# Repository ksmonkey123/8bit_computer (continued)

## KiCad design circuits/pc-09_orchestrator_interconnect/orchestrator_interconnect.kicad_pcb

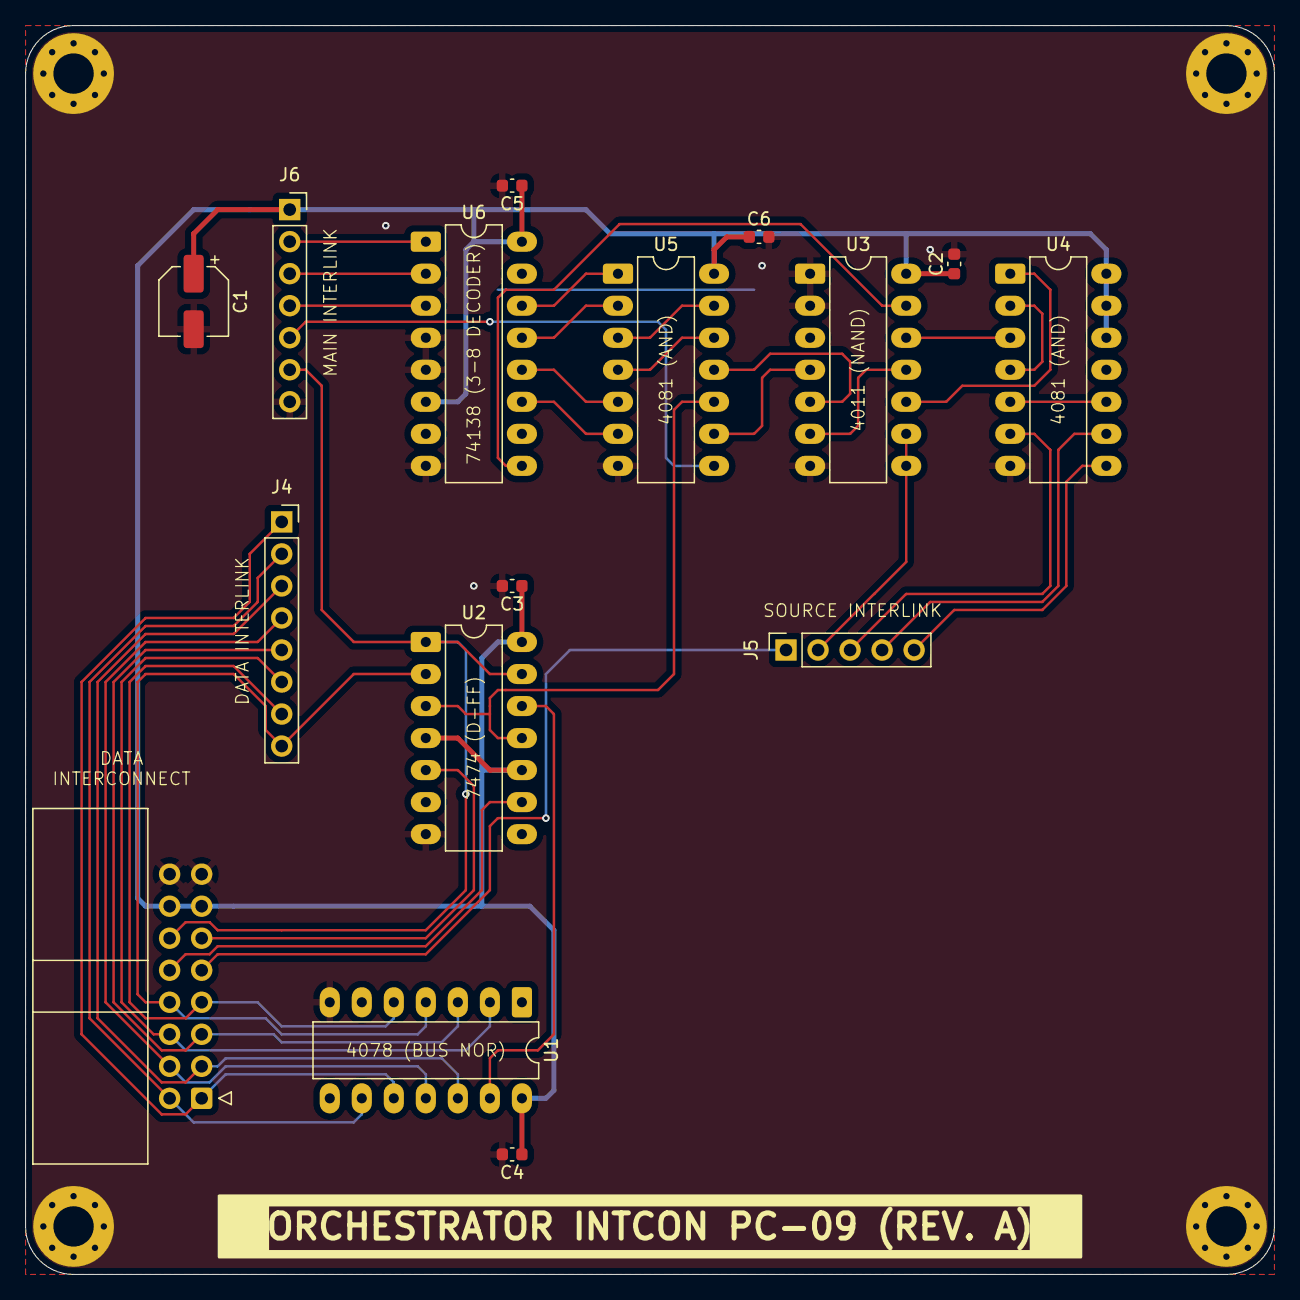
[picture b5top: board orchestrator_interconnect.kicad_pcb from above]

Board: 2 copper layers, 99.1 x 99.1 mm, 20 parts (0 on the bottom side), 38 nets.

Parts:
C1: C_Polarized; CP_Elec_5x5.3
C2, C3, C4, C5, C6: C; C_0603_1608Metric
DATA_BUS1: Conn_01x16; IDC-Header_2x08_P2.54mm_Horizontal
H1, H2, H3, H4: MountingHole_Pad; MountingHole_3.2mm_M3_Pad_Via
J4: Conn_01x08; PinSocket_1x08_P2.54mm_Vertical
J5: Conn_01x05; PinSocket_1x05_P2.54mm_Vertical
J6: Conn_01x07; PinSocket_1x07_P2.54mm_Vertical
U1: 4078; DIP-14_W7.62mm_LongPads
U2: 74HC74; DIP-14_W7.62mm_LongPads
U3: 4011; DIP-14_W7.62mm_LongPads
U4, U5: 4081; DIP-14_W7.62mm_LongPads
U6: 74HC138; DIP-16_W7.62mm_LongPads

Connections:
/carryFlag: DATA_BUS1.9, J5.1
/clock: J6.5, U5.8
/data0: DATA_BUS1.1, J4.1, U1.10
/data1: DATA_BUS1.2, J4.2, U1.9
/data2: DATA_BUS1.3, J4.3, U1.12
/data3: DATA_BUS1.4, J4.4, U1.11
/data4: DATA_BUS1.5, J4.5, U1.3
/data5: DATA_BUS1.6, J4.6, U1.2
/data6: DATA_BUS1.7, J4.7, U1.5
/data7: DATA_BUS1.8, J4.8, U1.4, U2.2 (D)
/dsrc0: J5.2, U3.8, U3.9
/dsrc1: J5.3, U4.6
/dsrc2: J5.4, U4.9
/dsrc3: J5.5, U4.8
/dtgt0: J6.2, U6.1 (A0)
/dtgt1: J6.3, U6.2 (A1)
/dtgt2: J6.4, U6.3 (A2)
/minusFlag: DATA_BUS1.11, U2.5 (Q)
/updateFlags: U2.3 (C), U2.11 (C), U5.10
/zeroFlag: DATA_BUS1.10, U2.9 (Q)
/zeroOnBus: U1.13, U2.12 (D)
/~reset: DATA_BUS1.12, J6.6, U2.1 (~R), U2.13 (~R)
GND: C1.2, C2.2, C3.2, C4.2, C5.2, C6.2, DATA_BUS1.15, DATA_BUS1.16, H1.1, H2.1, H3.1, H4.1, J6.7, U1.7 (Vss), U2.7 (GND), U3.1, U3.2, U3.7 (VSS), U4.7 (VSS), U5.7 (VSS), U6.4 (~E0), U6.5 (~E1), U6.8 (GND)
unnamed: U3.4, U5.9
unnamed: U3.5, U5.11
unnamed: U3.10, U4.1
unnamed: U3.6, U3.11
unnamed: U3.12, U4.3
unnamed: U4.2, U4.4
unnamed: U4.5, U4.10
unnamed: U5.4, U5.12
unnamed: U5.3, U5.13
unnamed: U5.1, U6.14 (~Y1)
unnamed: U5.2, U6.13 (~Y2)
unnamed: U5.5, U6.12 (~Y3)
unnamed: U5.6, U6.11 (~Y4)
unnamed: U3.13, U6.9 (~Y6)
VCC: C1.1, C2.1, C3.1, C4.1, C5.1, C6.1, DATA_BUS1.13, DATA_BUS1.14, J6.1, U1.14 (Vdd), U2.4 (~S), U2.10 (~S), U2.14 (VCC), U3.14 (VDD), U4.12, U4.13, U4.14 (VDD), U5.14 (VDD), U6.6 (E2), U6.16 (VCC)

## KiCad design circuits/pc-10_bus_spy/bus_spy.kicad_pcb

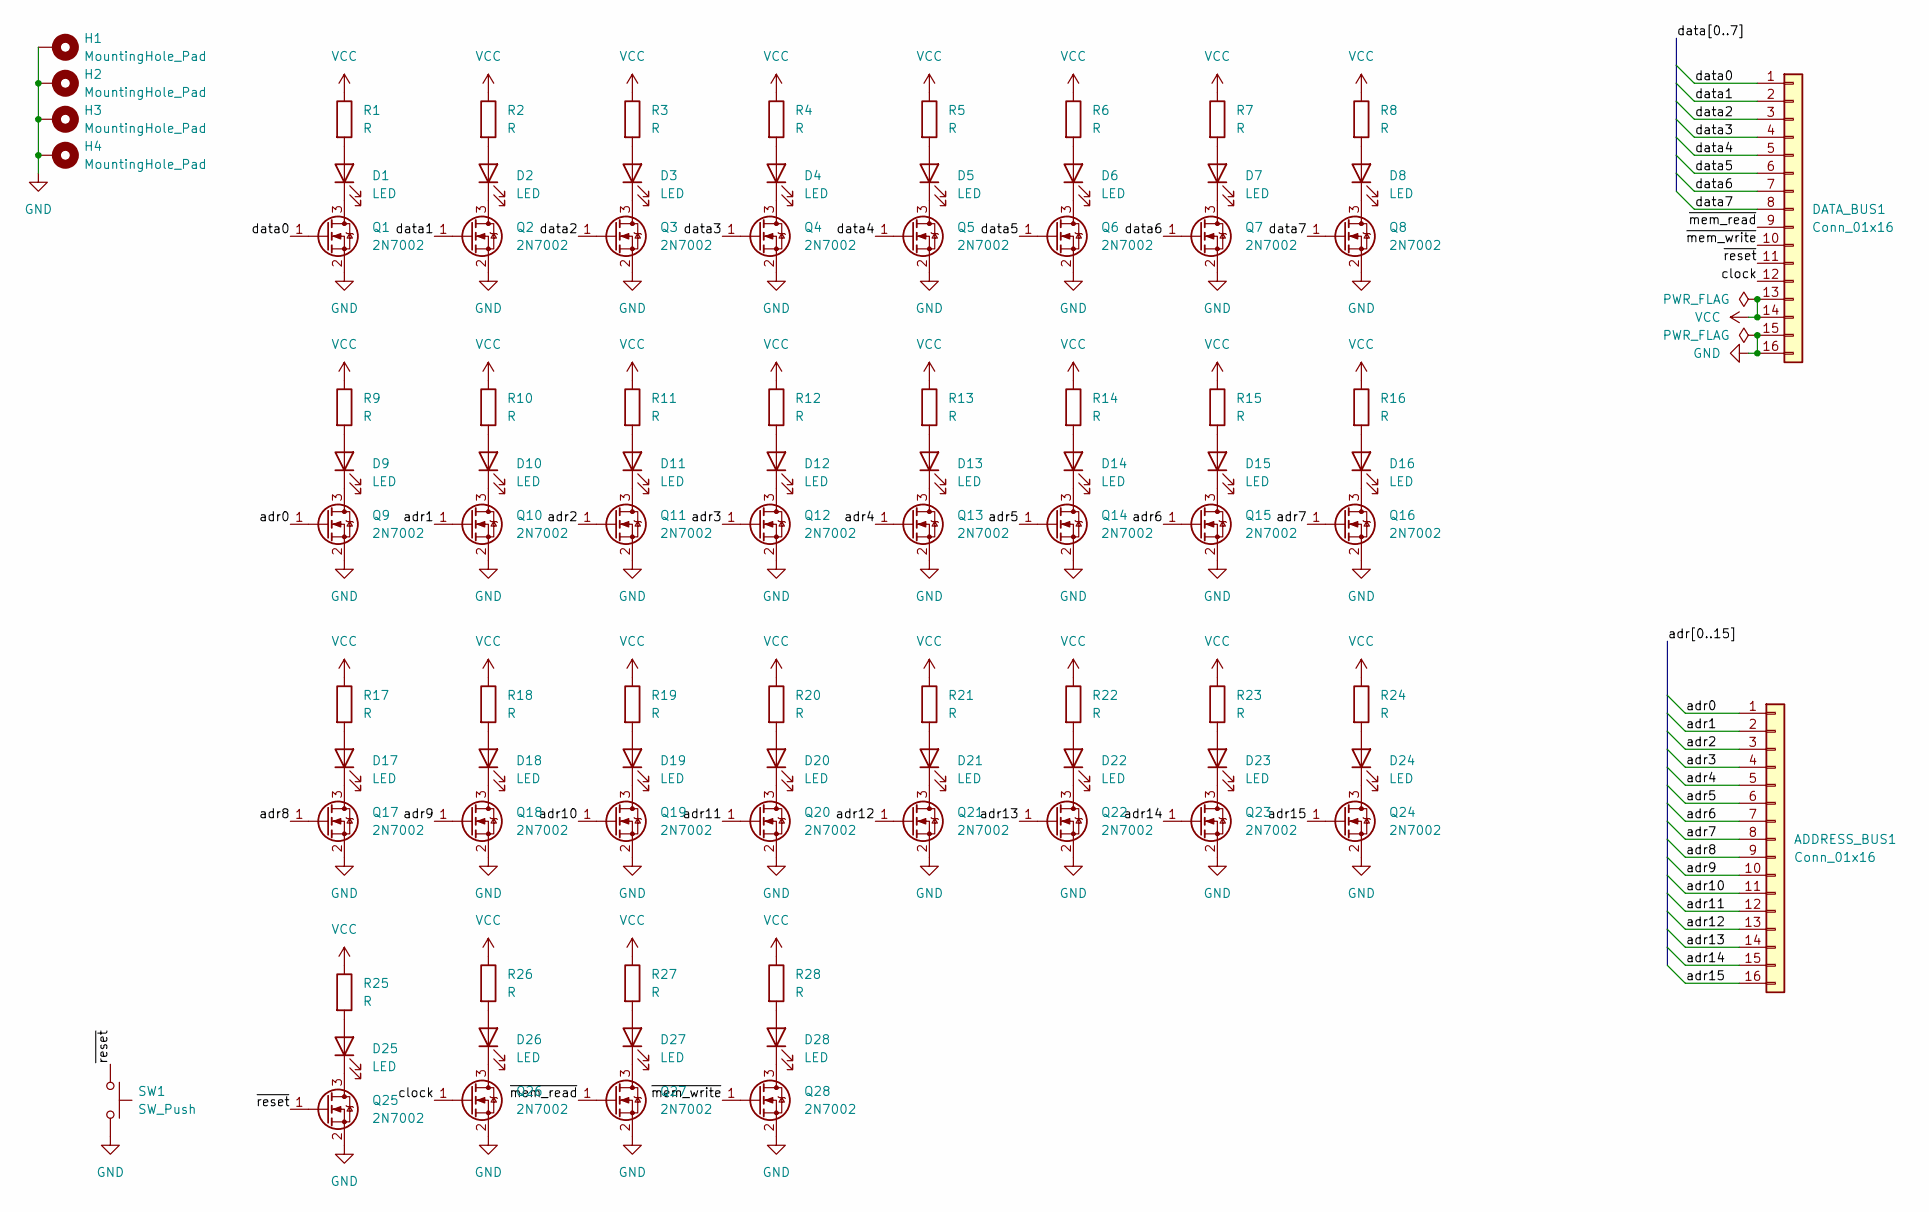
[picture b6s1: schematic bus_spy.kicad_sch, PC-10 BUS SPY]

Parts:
ADDRESS_BUS1: Conn_01x16; IDC-Header_2x08_P2.54mm_Horizontal
D1, D2, D3, D4, D5, D6, D7, D8, D9, D10, D11, D12, D13, D14, D15, D16, D17, D18, D19, D20, D21, D22, D23, D24, D25, D26, D27, D28: LED; LED_0603_1608Metric
DATA_BUS1: Conn_01x16; IDC-Header_2x08_P2.54mm_Horizontal
H1, H2, H3, H4: MountingHole_Pad; MountingHole_3.2mm_M3_Pad_Via
Q1, Q2, Q3, Q4, Q5, Q6, Q7, Q8, Q9, Q10, Q11, Q12, Q13, Q14, Q15, Q16, Q17, Q18, Q19, Q20, Q21, Q22, Q23, Q24, Q25, Q26, Q27, Q28: 2N7002; SOT-23
R1, R2, R3, R4, R5, R6, R7, R8, R9, R10, R11, R12, R13, R14, R15, R16, R17, R18, R19, R20, R21, R22, R23, R24, R25, R26, R27, R28: R; R_0603_1608Metric
SW1: SW_Push; SW_PUSH_6mm

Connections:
/adr0: ADDRESS_BUS1.1, Q9.1 (G)
/adr1: ADDRESS_BUS1.2, Q10.1 (G)
/adr2: ADDRESS_BUS1.3, Q11.1 (G)
/adr3: ADDRESS_BUS1.4, Q12.1 (G)
/adr4: ADDRESS_BUS1.5, Q13.1 (G)
/adr5: ADDRESS_BUS1.6, Q14.1 (G)
/adr6: ADDRESS_BUS1.7, Q15.1 (G)
/adr7: ADDRESS_BUS1.8, Q16.1 (G)
/adr8: ADDRESS_BUS1.9, Q17.1 (G)
/adr9: ADDRESS_BUS1.10, Q18.1 (G)
/adr10: ADDRESS_BUS1.11, Q19.1 (G)
/adr11: ADDRESS_BUS1.12, Q20.1 (G)
/adr12: ADDRESS_BUS1.13, Q21.1 (G)
/adr13: ADDRESS_BUS1.14, Q22.1 (G)
/adr14: ADDRESS_BUS1.15, Q23.1 (G)
/adr15: ADDRESS_BUS1.16, Q24.1 (G)
/clock: DATA_BUS1.12, Q26.1 (G)
/data0: DATA_BUS1.1, Q1.1 (G)
/data1: DATA_BUS1.2, Q2.1 (G)
/data2: DATA_BUS1.3, Q3.1 (G)
/data3: DATA_BUS1.4, Q4.1 (G)
/data4: DATA_BUS1.5, Q5.1 (G)
/data5: DATA_BUS1.6, Q6.1 (G)
/data6: DATA_BUS1.7, Q7.1 (G)
/data7: DATA_BUS1.8, Q8.1 (G)
/~mem_read: DATA_BUS1.9, Q27.1 (G)
/~mem_write: DATA_BUS1.10, Q28.1 (G)
/~reset: DATA_BUS1.11, Q25.1 (G), SW1.1
GND: DATA_BUS1.15, DATA_BUS1.16, H1.1, H2.1, H3.1, H4.1, Q1.2 (S), Q2.2 (S), Q3.2 (S), Q4.2 (S), Q5.2 (S), Q6.2 (S), Q7.2 (S), Q8.2 (S), Q9.2 (S), Q10.2 (S), Q11.2 (S), Q12.2 (S), Q13.2 (S), Q14.2 (S), Q15.2 (S), Q16.2 (S), Q17.2 (S), Q18.2 (S), Q19.2 (S), Q20.2 (S), Q21.2 (S), Q22.2 (S), Q23.2 (S), Q24.2 (S), Q25.2 (S), Q26.2 (S), Q27.2 (S), Q28.2 (S), SW1.2; also elsewhere on the board
unnamed: D1.2 (A), R1.2
unnamed: D1.1 (K), Q1.3 (D)
unnamed: D2.2 (A), R2.2
unnamed: D2.1 (K), Q2.3 (D)
unnamed: D3.2 (A), R3.2
unnamed: D3.1 (K), Q3.3 (D)
unnamed: D4.2 (A), R4.2
unnamed: D4.1 (K), Q4.3 (D)
unnamed: D5.2 (A), R5.2
unnamed: D5.1 (K), Q5.3 (D)
unnamed: D6.2 (A), R6.2
unnamed: D6.1 (K), Q6.3 (D)
unnamed: D7.2 (A), R7.2
unnamed: D7.1 (K), Q7.3 (D)
unnamed: D8.2 (A), R8.2
unnamed: D8.1 (K), Q8.3 (D)
unnamed: D9.2 (A), R9.2
unnamed: D9.1 (K), Q9.3 (D)
unnamed: D10.2 (A), R10.2
unnamed: D10.1 (K), Q10.3 (D)
unnamed: D11.2 (A), R11.2
unnamed: D11.1 (K), Q11.3 (D)
unnamed: D12.2 (A), R12.2
unnamed: D12.1 (K), Q12.3 (D)
unnamed: D13.2 (A), R13.2
unnamed: D13.1 (K), Q13.3 (D)
unnamed: D14.2 (A), R14.2
unnamed: D14.1 (K), Q14.3 (D)
unnamed: D15.2 (A), R15.2
unnamed: D15.1 (K), Q15.3 (D)
unnamed: D16.2 (A), R16.2
unnamed: D16.1 (K), Q16.3 (D)
unnamed: D17.2 (A), R17.2
unnamed: D17.1 (K), Q17.3 (D)
unnamed: D18.2 (A), R18.2
unnamed: D18.1 (K), Q18.3 (D)
unnamed: D19.2 (A), R19.2
unnamed: D19.1 (K), Q19.3 (D)
unnamed: D20.2 (A), R20.2
unnamed: D20.1 (K), Q20.3 (D)
unnamed: D21.2 (A), R21.2
unnamed: D21.1 (K), Q21.3 (D)
unnamed: D22.2 (A), R22.2
unnamed: D22.1 (K), Q22.3 (D)
unnamed: D23.2 (A), R23.2
unnamed: D23.1 (K), Q23.3 (D)
unnamed: D24.2 (A), R24.2
unnamed: D24.1 (K), Q24.3 (D)
unnamed: D25.2 (A), R25.2
unnamed: D25.1 (K), Q25.3 (D)
unnamed: D26.2 (A), R26.2
unnamed: D26.1 (K), Q26.3 (D)
unnamed: D27.2 (A), R27.2
unnamed: D27.1 (K), Q27.3 (D)
unnamed: D28.2 (A), R28.2
unnamed: D28.1 (K), Q28.3 (D)
VCC: DATA_BUS1.13, DATA_BUS1.14, R1.1, R2.1, R3.1, R4.1, R5.1, R6.1, R7.1, R8.1, R9.1, R10.1, R11.1, R12.1, R13.1, R14.1, R15.1, R16.1, R17.1, R18.1, R19.1, R20.1, R21.1, R22.1, R23.1, R24.1, R25.1, R26.1, R27.1, R28.1; also elsewhere on the board

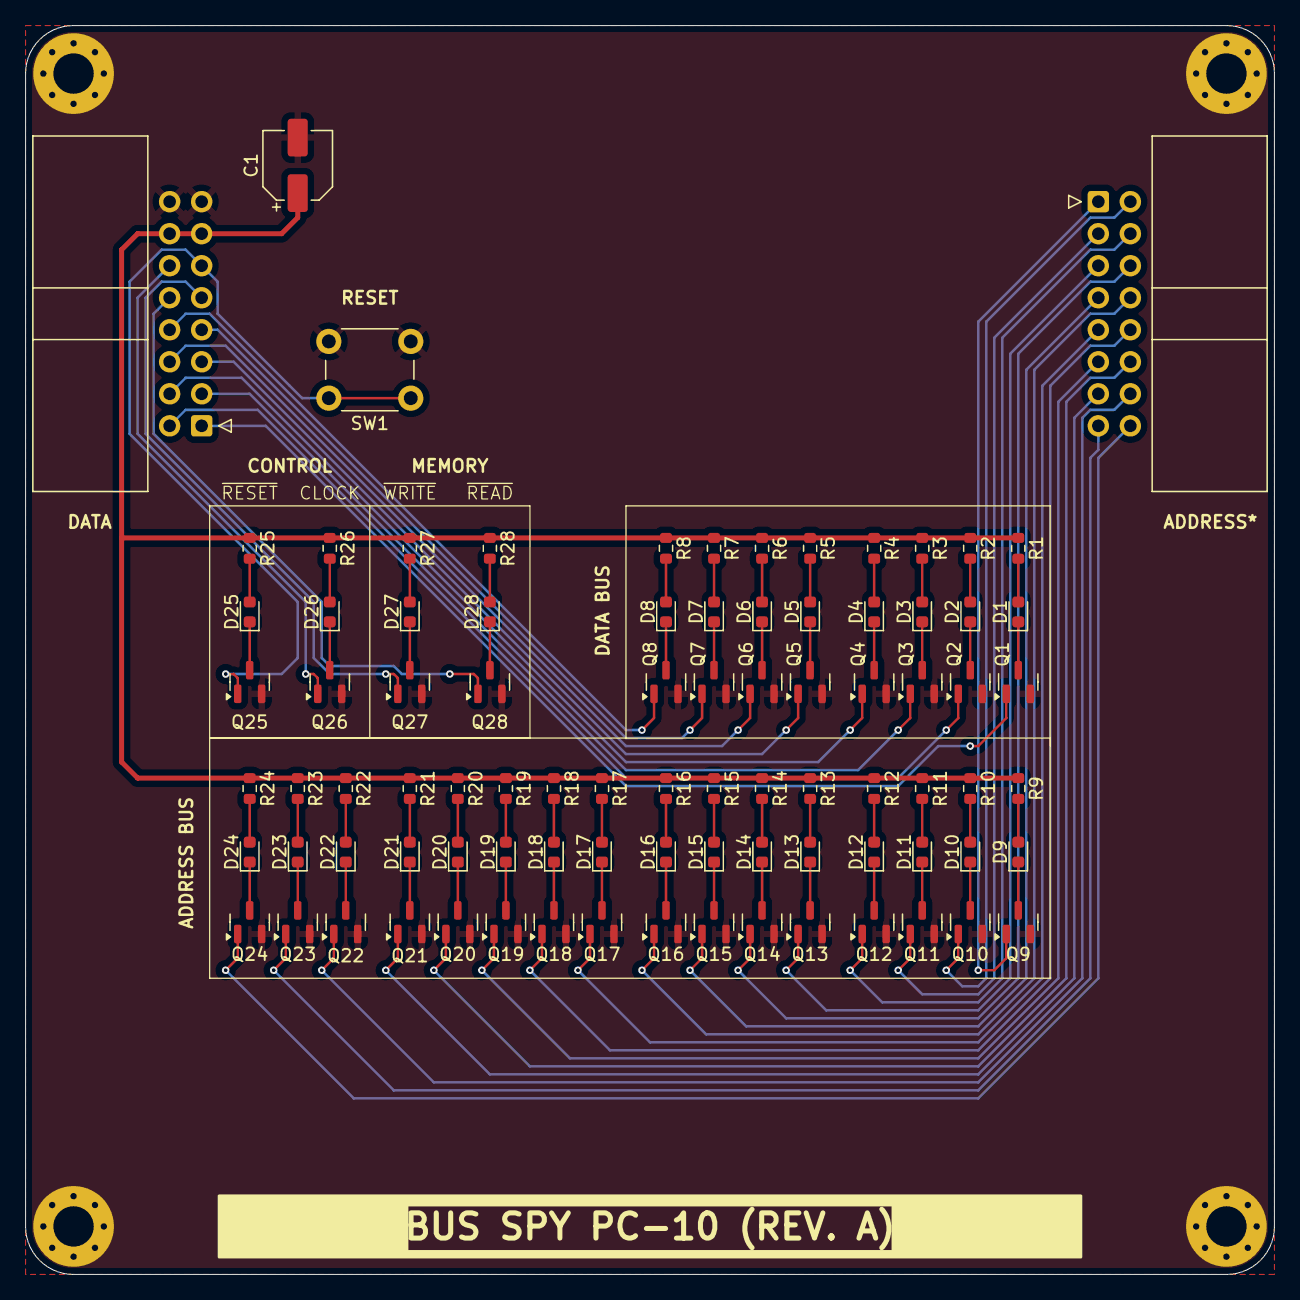
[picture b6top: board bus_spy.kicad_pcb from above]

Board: 2 copper layers, 99.1 x 99.1 mm, 92 parts (0 on the bottom side), 86 nets.

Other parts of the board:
C1: C_Polarized; CP_Elec_5x5.3

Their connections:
GND: C1.2; also elsewhere on the board
VCC: C1.1; also elsewhere on the board

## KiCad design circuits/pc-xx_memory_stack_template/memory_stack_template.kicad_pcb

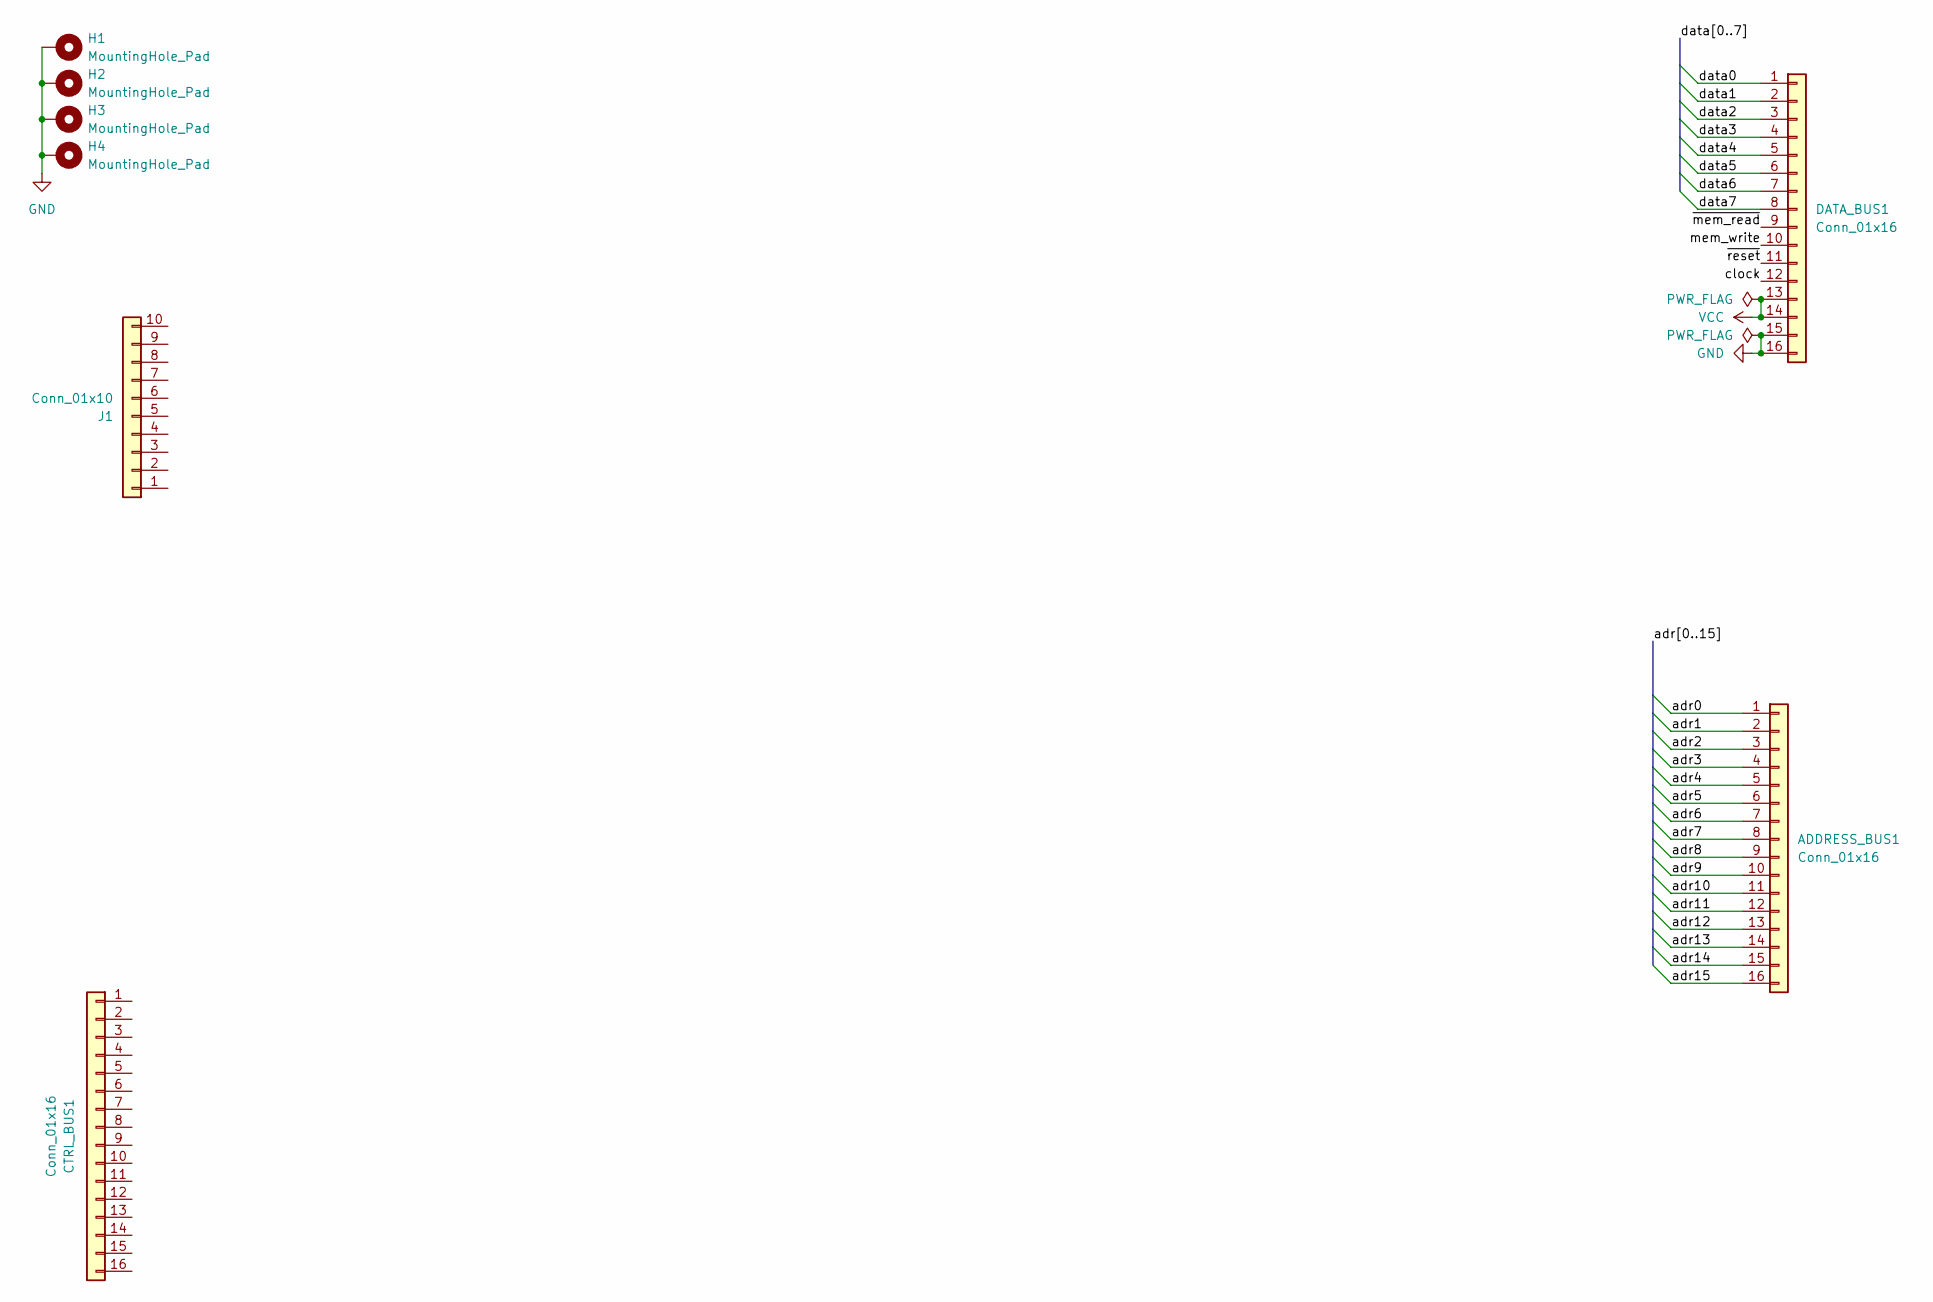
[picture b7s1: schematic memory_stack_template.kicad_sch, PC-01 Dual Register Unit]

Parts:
ADDRESS_BUS1: Conn_01x16; IDC-Header_2x08_P2.54mm_Horizontal
CTRL_BUS1: Conn_01x16; IDC-Header_2x08_P2.54mm_Horizontal
DATA_BUS1: Conn_01x16; IDC-Header_2x08_P2.54mm_Horizontal
H1, H2, H3, H4: MountingHole_Pad; MountingHole_3.2mm_M3_Pad_Via
J1: Conn_01x10; IDC-Header_2x05_P2.54mm_Horizontal

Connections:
/adr0: ADDRESS_BUS1.1
/adr1: ADDRESS_BUS1.2
/adr2: ADDRESS_BUS1.3
/adr3: ADDRESS_BUS1.4
/adr4: ADDRESS_BUS1.5
/adr5: ADDRESS_BUS1.6
/adr6: ADDRESS_BUS1.7
/adr7: ADDRESS_BUS1.8
/adr8: ADDRESS_BUS1.9
/adr9: ADDRESS_BUS1.10
/adr10: ADDRESS_BUS1.11
/adr11: ADDRESS_BUS1.12
/adr12: ADDRESS_BUS1.13
/adr13: ADDRESS_BUS1.14
/adr14: ADDRESS_BUS1.15
/adr15: ADDRESS_BUS1.16
/clock: DATA_BUS1.12
/data0: DATA_BUS1.1
/data1: DATA_BUS1.2
/data2: DATA_BUS1.3
/data3: DATA_BUS1.4
/data4: DATA_BUS1.5
/data5: DATA_BUS1.6
/data6: DATA_BUS1.7
/data7: DATA_BUS1.8
/mem_write: DATA_BUS1.10
/~mem_read: DATA_BUS1.9
/~reset: DATA_BUS1.11
GND: DATA_BUS1.15, DATA_BUS1.16, H1.1, H2.1, H3.1, H4.1
VCC: DATA_BUS1.13, DATA_BUS1.14

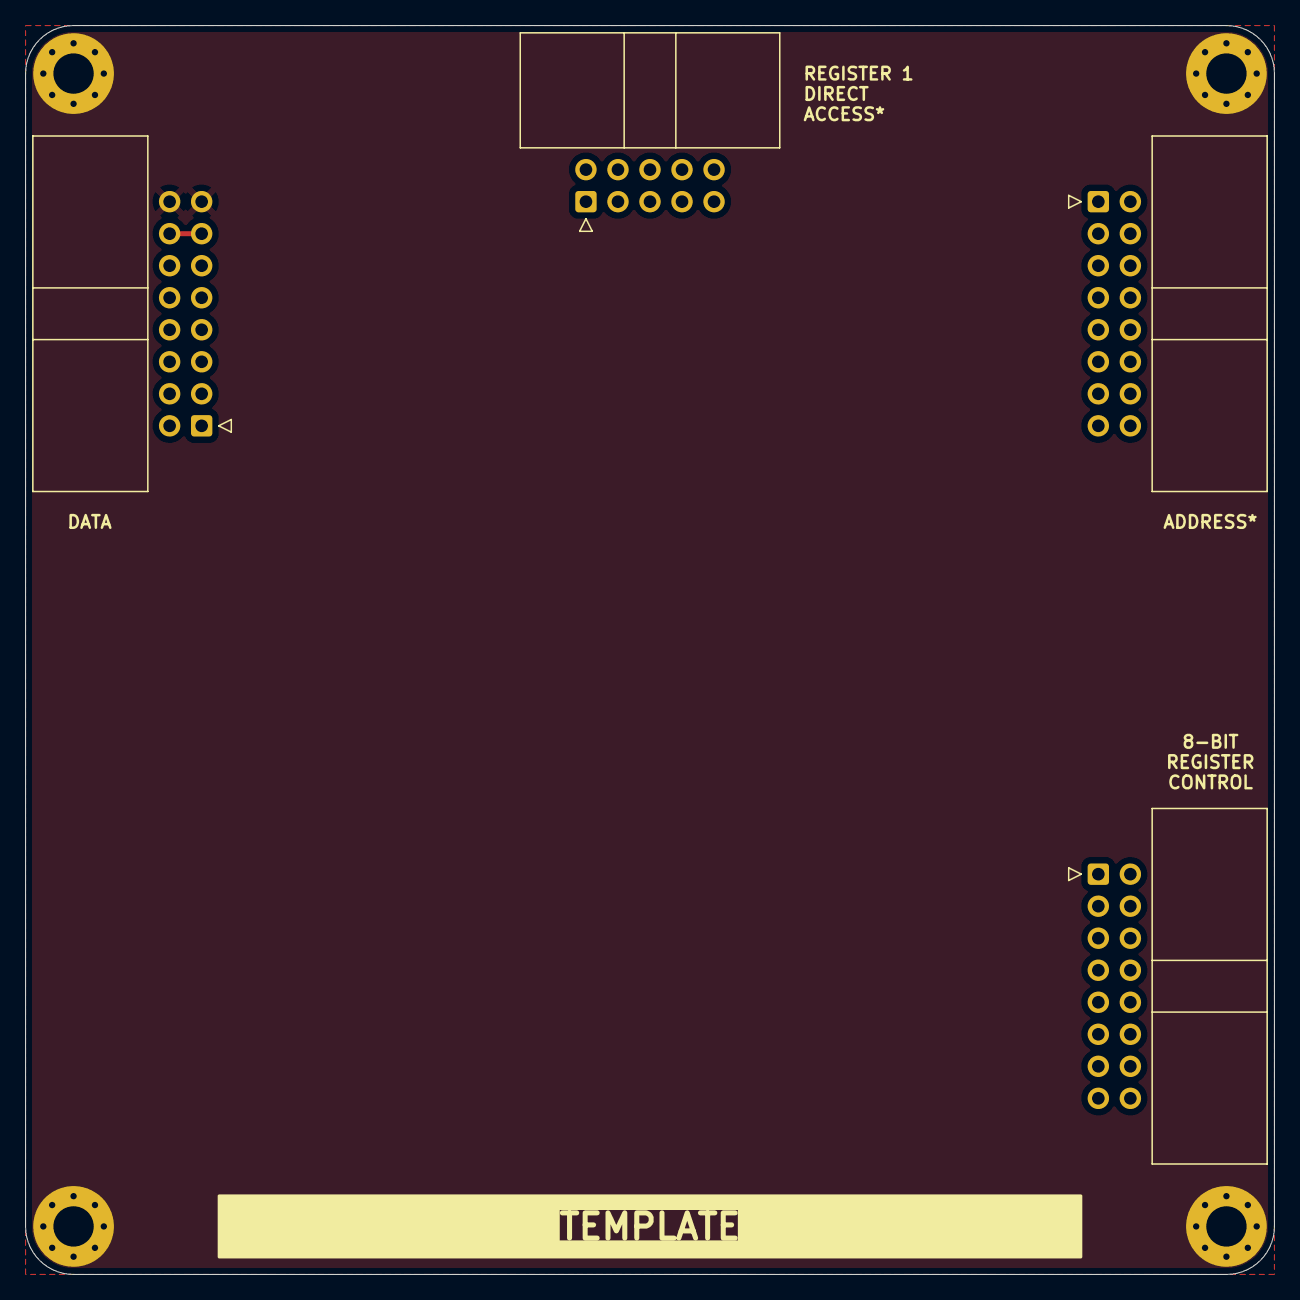
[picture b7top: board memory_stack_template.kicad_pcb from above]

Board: 2 copper layers, 99.1 x 99.1 mm, 8 parts (0 on the bottom side), 2 nets.
